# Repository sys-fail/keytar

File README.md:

# keytar
key-hand-orthoganally-respectful-device

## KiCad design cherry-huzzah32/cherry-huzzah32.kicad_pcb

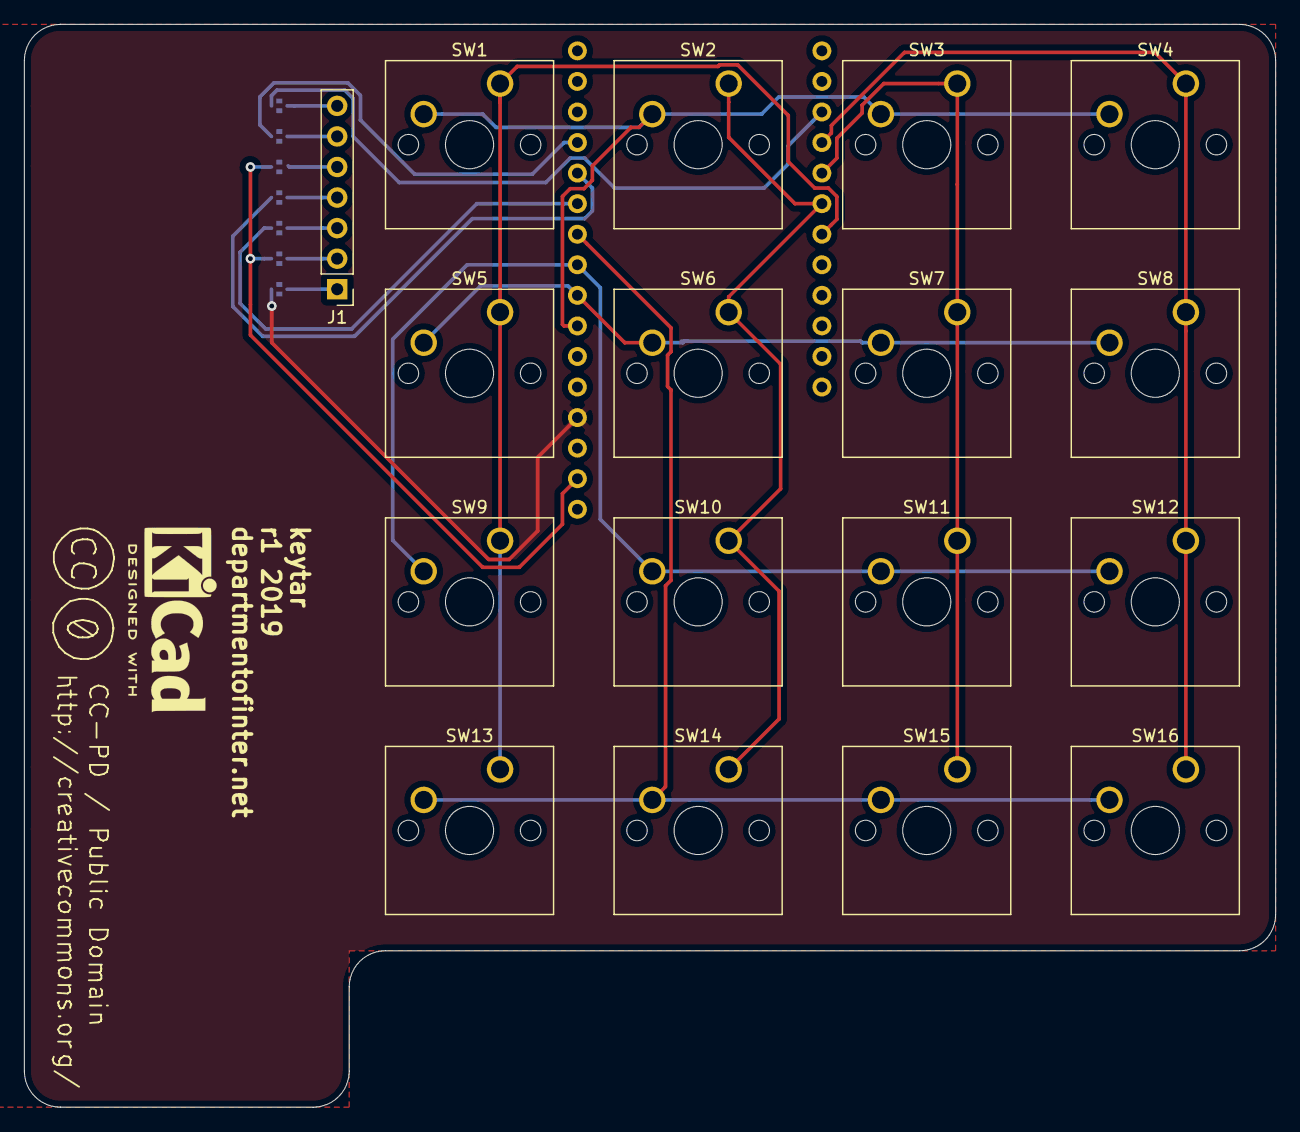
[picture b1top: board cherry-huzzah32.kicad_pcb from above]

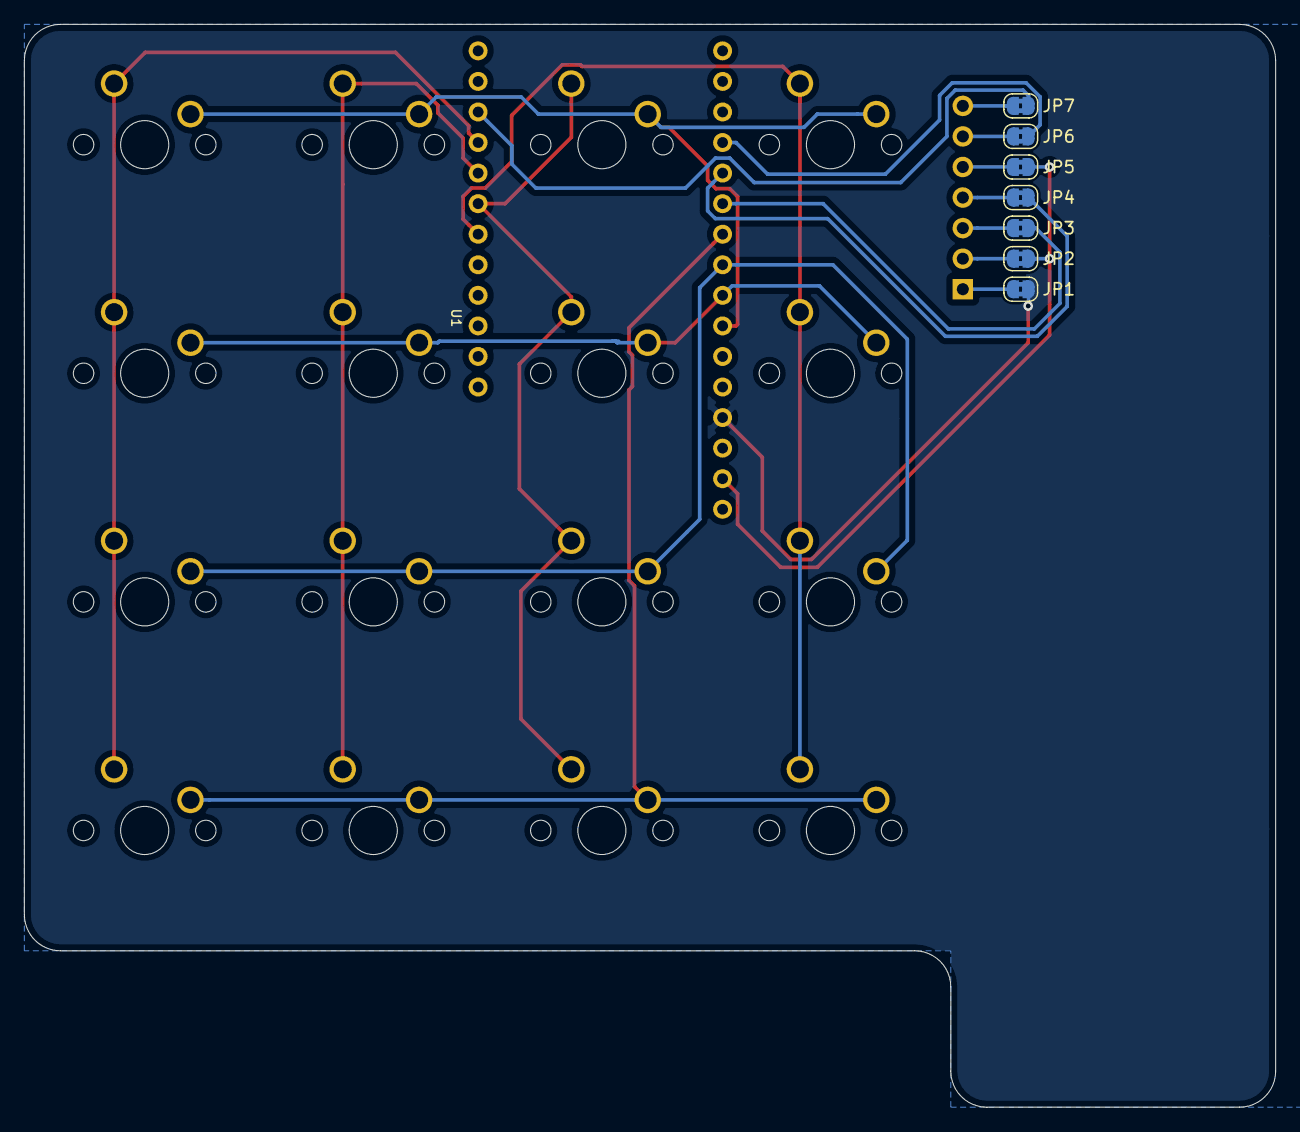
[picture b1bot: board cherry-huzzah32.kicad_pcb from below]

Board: 2 copper layers, 104.0 x 90.0 mm, 25 parts (8 on the bottom side), 21 nets.

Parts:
J1: Conn_01x07; PinHeader_1x07_P2.54mm_Vertical
JP1, JP2, JP3, JP4, JP5, JP6, JP7: SolderJumper_2_Bridged; SolderJumper-2_P1.3mm_Bridged2Bar_RoundedPad1.0x1.5mm
SW1, SW2, SW3, SW4, SW5, SW6, SW7, SW8, SW9, SW10, SW11, SW12, SW13, SW14, SW15, SW16: SW_Push; SW_Cherry_MX_1.00u_PCB
U1: adafruit_feather_huzzah32; Adafruit_Feather_HUZZAH32

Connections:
+3V3: JP2.2, JP5.2, U1.2
/CS_SSD: JP7.2, U1.19
/MC1: SW1.1, SW5.1, SW9.1, SW13.1, U1.23
/MC2: SW2.1, SW6.1, SW10.1, SW14.1, U1.22
/MC3: SW3.1, SW7.1, SW11.1, SW15.1, U1.21
/MC4: SW4.1, SW8.1, SW12.1, SW16.1, U1.20
/MISO: JP6.2, U1.13
/MOSI: JP4.2, U1.12
/MR1: SW1.2, SW2.2, SW3.2, SW4.2, U1.7
/MR2: SW5.2, SW6.2, SW7.2, SW8.2, U1.8
/MR3: SW9.2, SW10.2, SW11.2, SW12.2, U1.9
/MR4: SW13.2, SW14.2, SW15.2, SW16.2, U1.10
/SCK: JP3.2, U1.11
GND: JP1.2, U1.4
unnamed: J1.1, JP1.1
unnamed: J1.2, JP2.1
unnamed: J1.3, JP3.1
unnamed: J1.4, JP4.1
unnamed: J1.5, JP5.1
unnamed: J1.6, JP6.1
unnamed: J1.7, JP7.1

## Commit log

2019-12-04 hope i didn't miss anything important
2019-12-04 fuck arduino
2019-12-05 it's ocaml time
2020-01-19 ceytar functions
2020-04-09 this is how i found, hopefully what i am running on the board now
